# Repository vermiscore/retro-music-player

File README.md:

# 🎵 Retro Music Player

A Raspberry Pi Zero 2W-based music player with a retro aesthetic. Features a touch display showing the current track, animated landscape scenes, and a clock — all controllable via a web UI from any device on your network.

Built as a Mother's Day gift 💐

---

---

## ✨ Features

| Feature | Status |
|---------|--------|
| OS setup & SSH access | ✅ |
| MPD music playback | ✅ |
| ILI9341 SPI touch display | ✅ |
| Auto-start on boot | ✅ |
| Tailscale remote access | ✅ |
| Web UI (Flask) | ✅ |
| Touch panel controls | ✅ |
| Multi-screen UI (Home / Music / Clock / Photo / Mail / Scene) | ✅ |
| Landscape animation (auto-launch during playback) | ✅ |
| Photo gallery & slideshow | ✅ |
| Message feature (Web UI → display) | ✅ |
| Sky color changes by time of day | ✅ |
| AirPlay (shairport-sync) | ✅ |
| MAX98357A amp wiring & audio output | ✅ |
| C++ effects processing | ❌ |

---

## 🛠 Hardware

| Component | Details |
|-----------|---------|
| Raspberry Pi Zero 2WH | Main board |
| MAX98357A | I2S amplifier |
| ILI9341 2.4" display | SPI touch display (XPT2046 controller) |
| Speaker | 3W / 4Ω, JST-PH 2mm connector |
| microSD 32GB | Storage |
| Tactile switch | Power on/shutdown button |

---

## 🔌 Wiring

### ILI9341 Display + Touch (XPT2046)

| LCD Pin | Pi GPIO | Physical Pin | Notes |
|---------|---------|-------------|-------|
| VCC | 3.3V | Pin 1 | |
| GND | GND | Pin 6 | |
| CS | GPIO8 (CE0) | Pin 24 | Display CS |
| RESET | GPIO25 | Pin 22 | |
| DC | GPIO24 | Pin 18 | |
| SDI (MOSI) | GPIO10 | Pin 19 | |
| SCK | GPIO11 | Pin 23 | |
| LED | 3.3V | Pin 17 | |
| SDO (MISO) | not connected | — | |
| **T_DO** | **GPIO9** | **Pin 21** | Touch MISO |
| T_CS | GPIO7 (CE1) | Pin 26 | Touch CS |
| T_IRQ | GPIO17 | Pin 11 | Touch interrupt |
| **T_CLK** | **GPIO11 (shared)** | **Pin 23** | Shared with SCK |
| **T_DIN** | **GPIO10 (shared)** | **Pin 19** | Shared with MOSI |

> ⚠️ T_CLK and T_DIN are branched from Pin 23 and Pin 19 respectively.

### MAX98357A Amplifier

| Amp Pin | Pi GPIO | Physical Pin |
|---------|---------|-------------|
| VDD | 5V | Pin 2 |
| GND | GND | Pin 6 |
| BCLK | GPIO18 | Pin 12 |
| LRC | GPIO19 | Pin 35 |
| DIN | GPIO21 | Pin 40 |
| SD | 3.3V | — |

### Tactile Switch (Power Button)

```
Tactile switch
├── Terminal 1 → GPIO3 (Pin 5)
└── Terminal 2 → GND  (Pin 6)
```

**Button behavior:**
- Short press (device off) → Boot
- Long press (≥ 0.5s, device on) → Shutdown

---

## 💻 Software & File Structure

```
/home/pi/
├── main.py              ← Main loop (touch & display control)
├── touch.py             ← XPT2046 touch reader
├── app.py               ← Flask Web UI server
├── display.py
├── templates/
│   └── index.html       ← Web UI HTML
├── scenes/
│   ├── common.py        ← Shared colors, fonts, nav
│   ├── home.py          ← Home screen
│   ├── music.py         ← Music screen (playback controls)
│   ├── clock.py         ← Clock screen
│   ├── mail.py          ← Mail screen (message display)
│   ├── photo.py         ← Photo gallery & slideshow
│   ├── scene_select.py  ← Landscape selection screen
│   ├── landscape.py     ← Landscape animation
│   ├── rain.py
│   └── dance.py
├── music/               ← Music files (.mp3)
├── photos/              ← Photo files
└── messages.json        ← Message history
```

---

## ⚙️ OS & Setup

- **OS**: Raspberry Pi OS Bookworm Lite 64-bit (2024-11-19)
  - ⚠️ Avoid the latest Trixie (2025-12-04) — a bug in Imager prevents SSH/Wi-Fi settings from being applied correctly.
- **Default user**: `pi`

---

## 📦 Dependencies

```bash
sudo apt install python3-pip python3-dev python3-pil fonts-dejavu mpd mpc -y
pip3 install luma.lcd flask python-mpd2 spidev numpy --break-system-packages
```

---

## 🔧 Auto-Start (systemd)

### Display service (`main.py`)

```ini
# /etc/systemd/system/display.service
[Unit]
Description=Display Service
After=network.target

[Service]
ExecStart=/usr/bin/python3 /home/pi/main.py
WorkingDirectory=/home/pi
Restart=always
User=pi

[Install]
WantedBy=multi-user.target
```

### Flask Web UI service

```ini
# /etc/systemd/system/flask.service
[Unit]
Description=Flask Web UI
After=network.target

[Service]
ExecStart=/usr/bin/python3 /home/pi/app.py
WorkingDirectory=/home/pi
Restart=always
User=pi

[Install]
WantedBy=multi-user.target
```

### Enable both services

```bash
sudo systemctl enable display flask
sudo systemctl start display flask
```

---

## 🌐 Web UI

Access the Web UI from any browser on the same network:

```
http://<raspberry-pi-ip>:5000
```

**Features:** Music playback control, file management, photo upload, message sending, system controls.

> **Tip:** If the port is busy, run:
> ```bash
> sudo kill $(sudo fuser 5000/tcp 2>/dev/null)
> sudo systemctl start flask
> ```
> Or add this alias to `~/.bashrc` for convenience:
> ```bash
> alias fixflask='sudo kill $(sudo fuser 5000/tcp 2>/dev/null); sudo systemctl start flask'
> ```

---

## 🎵 MPD Configuration

### `/etc/mpd.conf` changes

```
music_directory "/home/pi/music"
bind_to_address "any"

audio_output {
    type        "alsa"
    name        "I2S Audio"
    device      "dmixer"
    mixer_type  "software"
}
```

### Permissions

```bash
chmod 755 /home/pi
sudo chown -R mpd:audio /home/pi/music
```

### Basic playback commands

```bash
mpc ls | mpc add   # Add all tracks
mpc play           # Play
mpc next           # Next track
mpc current        # Show current track
mpc stop           # Stop
```

---

## ➕ Adding Music

**Via SCP (recommended):**
```bash
scp ~/Downloads/song.mp3 pi@<raspberry-pi-ip>:/home/pi/music/
```

**Via Web UI:**
1. Web UI → Files tab → Upload files
2. Player tab → click "Scan Library"

> Either way, press **Scan Library** after adding files.

---

## 🔊 MAX98357A Troubleshooting

### Problem: No audio output

**Symptom:** Device appears in `aplay -l` but no sound.

**Root cause:** GPIO18 (BCLK) is not set to `PCM_CLK` by the overlay automatically.

**Diagnosis:**
```bash
pinctrl get 18,19,20,21
# GPIO18 should show PCM_CLK — if it shows "output", this is the bug
```

**Fix:**

1. Edit `/boot/firmware/config.txt`:
```
dtparam=i2s=on
# dtparam=audio=on   ← comment this out (conflicts with I2S)
dtoverlay=max98357a,no-sdmode
```

2. Create a systemd service to force GPIO18 to `PCM_CLK` on boot:

```ini
# /etc/systemd/system/i2s-fix.service
[Unit]
Description=Fix GPIO18 for I2S
After=multi-user.target

[Service]
Type=oneshot
ExecStartPre=/bin/sleep 3
ExecStart=/usr/bin/pinctrl set 18 a0
RemainAfterExit=yes

[Install]
WantedBy=multi-user.target
```

```bash
sudo systemctl enable i2s-fix
sudo systemctl start i2s-fix
```

> **Note:** If the display service reconfigures GPIO18 as output, restart both services:
> ```bash
> sudo systemctl restart display && sudo systemctl restart i2s-fix
> ```

---

### Problem: Buzzing / popping noise

**Root cause:** MAX98357A pops/buzzes when the I2S clock starts or stops.

**Fix:** Use ALSA `dmix` and continuously play silence to keep the I2S clock alive.

**1. Create `/etc/asound.conf`:**
```
pcm.dmixer {
    type dmix
    ipc_key 1024
    ipc_perm 0666
    slave {
        pcm "hw:0,0"
        rate 48000
        channels 2
    }
}
pcm.!default {
    type plug
    slave.pcm "dmixer"
}
```

**2. Create `/etc/systemd/system/aplay-silence.service`:**
```ini
[Unit]
Description=Play silence to keep I2S clock alive
After=sound.target

[Service]
ExecStart=/usr/bin/aplay -D dmixer -t raw -r 48000 -c 2 -f S16_LE /dev/zero
Restart=always

[Install]
WantedBy=multi-user.target
```

```bash
sudo systemctl enable aplay-silence
sudo systemctl daemon-reload
sudo reboot
```

---

## 📻 AirPlay Setup

```bash
sudo apt install shairport-sync -y
```

That's it — `shairport-sync` auto-starts on boot.

**Usage:**
1. Open Control Center on iPhone
2. Tap the AirPlay icon
3. Select `raspberrypi`
4. Play music from any app (Apple Music, Spotify, YouTube, etc.)

---

## 🖐 Touch Calibration

```python
X_MIN, X_MAX = 251, 3735
Y_MIN, Y_MAX = 220, 3842
```

Coordinate transform in `touch.py` (X/Y swap + X invert):
```python
x = SCREEN_W - int((y_raw - Y_MIN) / (Y_MAX - Y_MIN) * SCREEN_W)
y = int((x_raw - X_MIN) / (X_MAX - X_MIN) * SCREEN_H)
```

---

## 🗒 Known Issues

- Buzzing/popping noise is mitigated by the `aplay-silence` workaround above.
- If the Web UI port 5000 is occupied by another process (e.g. shairport-sync), change the Flask port to 5001.
- `systemd-networkd-wait-online.service` can block boot for 2+ minutes — disable it if startup is slow:
  ```bash
  sudo systemctl disable systemd-networkd-wait-online.service
  ```

---

## 📐 PCB

Designed in KiCad. Files are in the [`hardware/`](hardware/) directory.

- `music_player.kicad_pcb` — PCB layout
- `music_player.kicad_sch` — Schematic
- `gerber/` — Gerber files for PCB fabrication (e.g. JLCPCB)

---

## 📄 License

MIT License

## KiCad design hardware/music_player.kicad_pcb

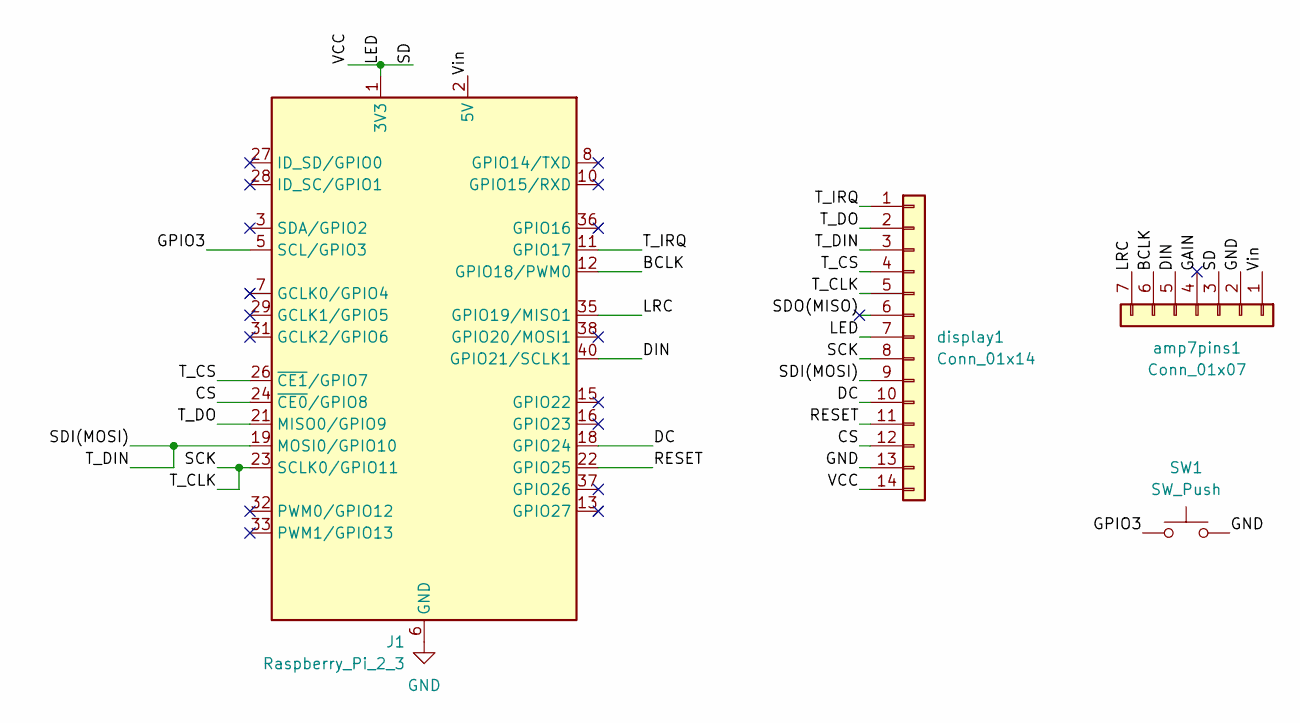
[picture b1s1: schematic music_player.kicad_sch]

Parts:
J1: Raspberry_Pi_2_3; PinSocket_2x20_P2.54mm_Vertical
SW1: SW_Push; SW_PUSH_6mm
amp7pins1: Conn_01x07; PinHeader_1x07_P2.54mm_Vertical
display1: Conn_01x14; PinSocket_1x14_P2.54mm_Vertical

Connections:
/BCLK: J1.12 (GPIO18/PWM0), amp7pins1.6
/CS: J1.24 (~CE0/GPIO8), display1.12
/DC: J1.18 (GPIO24), display1.10
/DIN: J1.40 (GPIO21/SCLK1), amp7pins1.5
/GAIN: amp7pins1.4
/GPIO3: J1.5 (SCL/GPIO3), SW1.1
/LED: J1.1 (3V3), J1.17 (3V3), amp7pins1.3, display1.7, display1.14
/LRC: J1.35 (GPIO19/MISO1), amp7pins1.7
/RESET: J1.22 (GPIO25), display1.11
/SCK: J1.23 (SCLK0/GPIO11), display1.5, display1.8
/SDI(MOSI): J1.19 (MOSI0/GPIO10), display1.3, display1.9
/SDO(MISO): display1.6
/T_CS: J1.26 (~CE1/GPIO7), display1.4
/T_DO: J1.21 (MISO0/GPIO9), display1.2
/T_IRQ: J1.11 (GPIO17), display1.1
/Vin: J1.2 (5V), J1.4 (5V), amp7pins1.1
GND: J1.6 (GND), J1.9 (GND), J1.14 (GND), J1.20 (GND), J1.25 (GND), J1.30 (GND), J1.34 (GND), J1.39 (GND), SW1.2, amp7pins1.2, display1.13

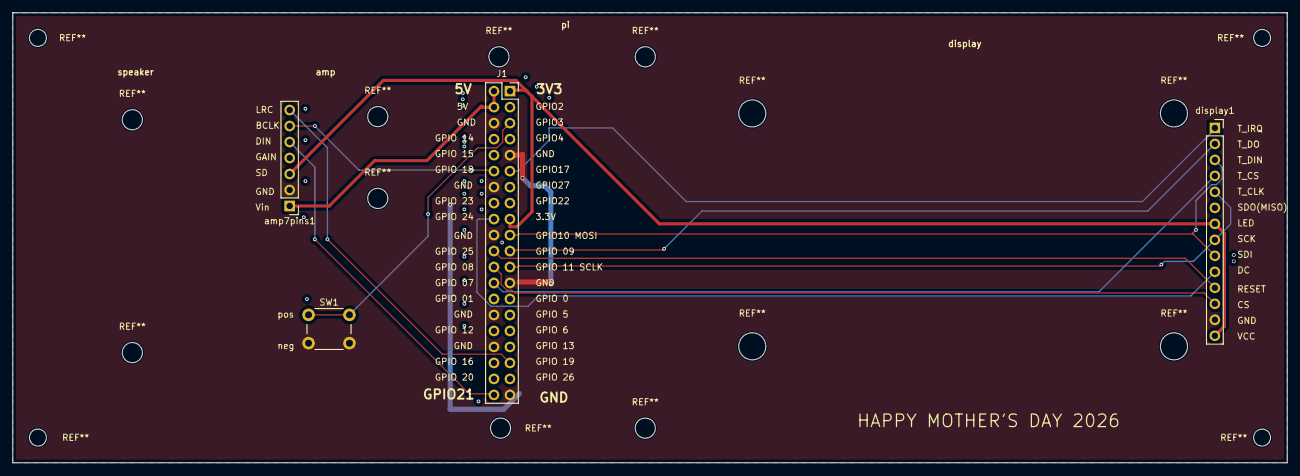
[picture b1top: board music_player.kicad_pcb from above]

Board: 2 copper layers, 202.5 x 71.5 mm, 4 parts (0 on the bottom side), 15 nets.

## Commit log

2026-04-08 update app.py and index.html - add scan library fix
2026-04-08 add genre selection with scroll, fix i2s on startup
2026-04-08 genre selection, i2s fix, scan library fix
2026-04-11 Add new scenes, cat mascot, system info screen, photo delete feature
2026-04-12 Fix mail notification, update dance bg, update scene descriptions
2026-04-22 Add README, hardware files, and photos
2026-04-22 Update README to remove landscape scenes feature
    Removed 'Additional landscape scenes (Rain / Night / Snow)' from the features list.
2026-04-22 Add images folder
2026-04-22 Fix image path in README
2026-04-22 Add PCB layout image to README
